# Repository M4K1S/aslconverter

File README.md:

# aslconverter

A wearable glove that reads hand shape and finger contact to recognize ASL fingerspelling letters, built on an ESP32-S3 with an on-device TinyML classifier.

## Overview

The glove combines three sensor types to distinguish letters that look identical on flex data alone:

- **5 flex sensors** (one per finger) measure how curled each finger is
- **4 touch sensors** (between adjacent fingers) detect direct finger-to-finger contact — needed for letters like F, O, T, and S, which have near-identical flex readings but differ in which fingers touch
- **1 IMU (MPU6050)** measures hand orientation via accelerometer, used to disambiguate handshape pairs that differ mainly by rotation (e.g. K vs. P, G vs. Q, H vs. U)

Sensor data streams over serial into a custom Edge Impulse model, which classifies static letter handshapes for on-device inference on the ESP32-S3.

## Repository structure

```
firmware/
  firmware.ino          Arduino sketch — sensor reading, calibration, serial output

hardware/
  pcb/kicad/
    asl_glove_pcb.kicad_sch    Schematic
    asl_glove_pcb.kicad_pcb    PCB layout
    asl_glove_pcb.kicad_pro    KiCad project file
    gerbers/                   Fabrication outputs (Gerbers, drill files, job file)
```

## Hardware

### PCB
2-layer board (FR-4, HASL finish, 1oz copper) designed in KiCad, hosting all sensor connectors and a socket header pair for an ESP32-S3 DevKit (Freenove ESP32-S3-WROOM). Fabricated via JLCPCB.

### Flex sensors
| Finger | GPIO |
|---|---|
| Thumb | 1 |
| Index | 2 |
| Middle | 4 |
| Ring | 5 |
| Pinky | 6 |

Each sensor forms a voltage divider with a 10kΩ resistor to GND; the midpoint feeds an ADC1-capable GPIO.

### Touch sensors
| Sensor | GPIO |
|---|---|
| Thumb–Index (T-I) | 7 |
| Index–Middle (I-M) | 15 |
| Middle–Ring (M-R) | 16 |
| Ring–Pinky (R-P) | 17 |

Digital inputs using the ESP32's internal pull-up (`INPUT_PULLUP`) — no external resistors required. Reads LOW when fingers touch (shorted to GND), HIGH when apart.

### IMU
MPU6050 over I2C — SDA on GPIO8, SCL on GPIO9 (ESP32-S3 default I2C pins).

## Firmware (`firmware/firmware.ino`)

- **Calibration on boot** — straight/bent reference per flex sensor, then a neutral-position accelerometer offset, both prompted interactively over serial
- **EMA filtering** on flex readings (α = 0.15) to smooth sensor noise
- **Bad-reading rejection** — a raw ADC value of 0 is treated as a glitch and skipped, holding the last valid filtered reading instead of reporting a false zero
- **CSV streaming** over serial at ~32Hz, one line per sample:

```
thumb,index,middle,ring,pinky,ti,im,mr,rp,accelX,accelY,accelZ,gyroX,gyroY,gyroZ
```

## Machine learning pipeline

Model built and trained in Edge Impulse:

- **Data collection:** `edge-impulse-data-forwarder` streams the serial CSV output into labeled training samples, one short recording per letter
- **Input features:** 12 of the 15 streamed values (flex ×5, touch ×4, accel ×3) — gyro is excluded from the static-letter model, since it only carries signal during motion, not held poses
- **Processing block:** Flatten (mean/min/max/RMS per axis), with feature normalization (StandardScaler) enabled to put flex (0–100), touch (0/1), and accel (small decimals) on comparable scales
- **Learning block:** Classification (Keras neural network)
- **Deployment:** exported as an Arduino library for fully on-device inference — no network connection required at runtime

### Scope

Targets the **24 static fingerspelling letters** (A–Z excluding J and Z). J and Z are motion-based letters — traced in the air rather than held — and are planned as a separate detection path using gyroscope motion-burst thresholds rather than static classification.

## Known issues / in progress

- **Flex sensor drift within a session** — sensors can shift slightly inside their glove mounting over time, causing readings for the same handshape to gradually change during a long recording session. Mitigation in progress: securing sensor mounting points and/or periodic in-session recalibration.
- Full 24-letter training data collection is in progress.

## Status

🚧 Active development — hardware fabricated (5 flex + 4 touch + IMU), firmware stable, ML pipeline validated end-to-end on a 2-letter test set. Full alphabet data collection and training in progress.

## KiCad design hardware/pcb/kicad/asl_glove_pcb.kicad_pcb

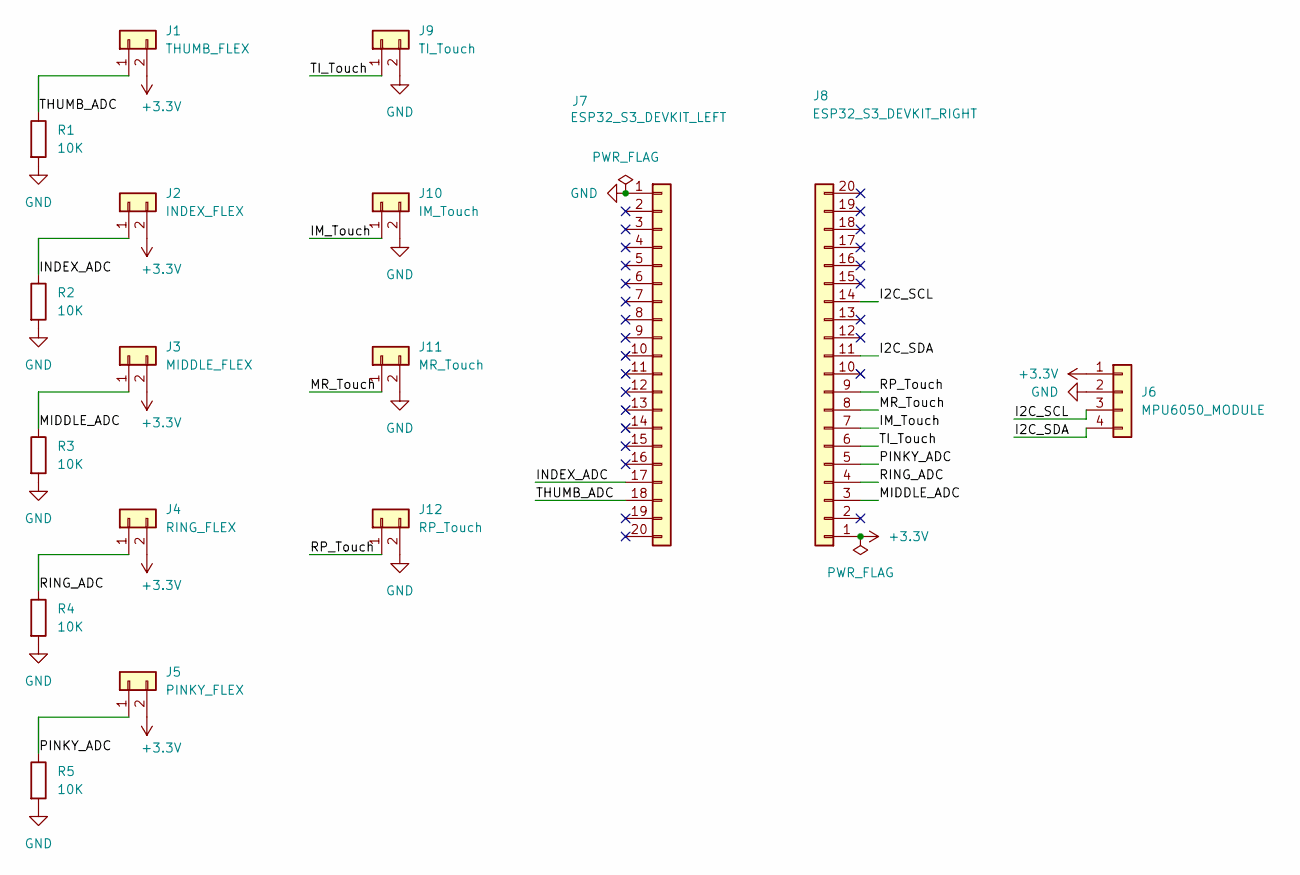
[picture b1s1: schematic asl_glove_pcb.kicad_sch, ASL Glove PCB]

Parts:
J1: THUMB_FLEX; PinHeader_1x02_P2.54mm_Vertical
J2: INDEX_FLEX; PinHeader_1x02_P2.54mm_Vertical
J3: MIDDLE_FLEX; PinHeader_1x02_P2.54mm_Vertical
J4: RING_FLEX; PinHeader_1x02_P2.54mm_Vertical
J5: PINKY_FLEX; PinHeader_1x02_P2.54mm_Vertical
J6: MPU6050_MODULE; PinHeader_1x04_P2.54mm_Vertical
J7: ESP32_S3_DEVKIT_LEFT; PinHeader_1x20_P2.54mm_Vertical
J8: ESP32_S3_DEVKIT_RIGHT; PinHeader_1x20_P2.54mm_Vertical
J9: TI_Touch; PinHeader_1x02_P2.54mm_Vertical
J10: IM_Touch; PinHeader_1x02_P2.54mm_Vertical
J11: MR_Touch; PinHeader_1x02_P2.54mm_Vertical
J12: RP_Touch; PinHeader_1x02_P2.54mm_Vertical
R1, R2, R3, R4, R5: 10K; R_Axial_DIN0207_L6.3mm_D2.5mm_P7.62mm_Horizontal

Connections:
+3.3V: J1.2, J2.2, J3.2, J4.2, J5.2, J6.1, J8.1
/I2C_SCL: J6.3, J8.14
/I2C_SDA: J6.4, J8.11
/IM_Touch: J8.7, J10.1
/INDEX_ADC: J2.1, J7.17, R2.1
/MIDDLE_ADC: J3.1, J8.3, R3.1
/MR_Touch: J8.8, J11.1
/PINKY_ADC: J5.1, J8.5, R5.1
/RING_ADC: J4.1, J8.4, R4.1
/RP_Touch: J8.9, J12.1
/THUMB_ADC: J1.1, J7.18, R1.1
/TI_Touch: J8.6, J9.1
GND: J6.2, J7.1, J9.2, J10.2, J11.2, J12.2, R1.2, R2.2, R3.2, R4.2, R5.2

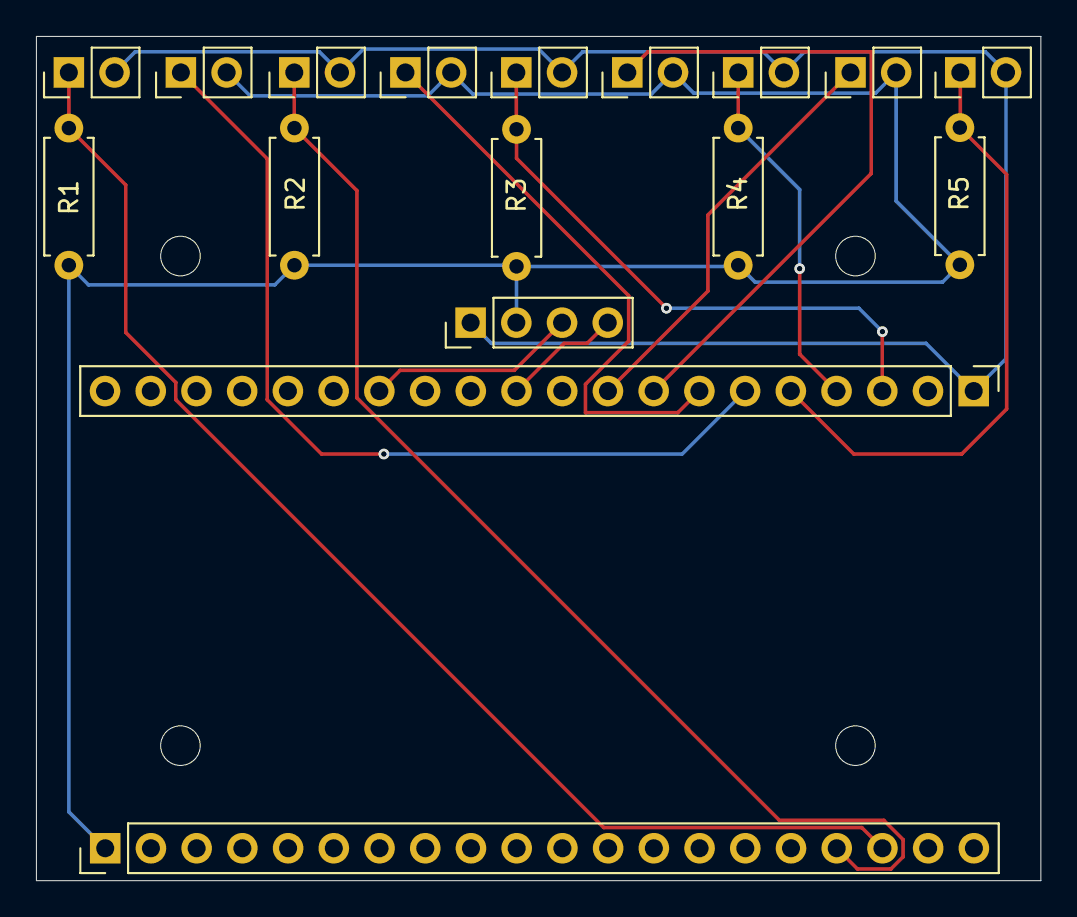
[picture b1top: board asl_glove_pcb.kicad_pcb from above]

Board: 2 copper layers, 55.8 x 46.9 mm, 17 parts (0 on the bottom side), 13 nets.
